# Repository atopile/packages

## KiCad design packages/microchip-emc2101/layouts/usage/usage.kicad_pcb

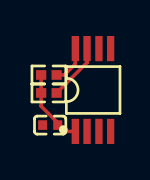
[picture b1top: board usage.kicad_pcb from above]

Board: 2 copper layers, 4 parts (0 on the bottom side), 4 nets.

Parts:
C1: [capacitance: unknown]; C0402
R1, R2: [resistance: unknown]; R0402
U1: MSOP-8_L3.0-W3.0-P0.65-LS4.9-BL

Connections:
SCL: R1.1, U1.8
SDA: R2.1, U1.7
hv: C1.1, R1.2, R2.2, U1.1
lv: C1.2, U1.5

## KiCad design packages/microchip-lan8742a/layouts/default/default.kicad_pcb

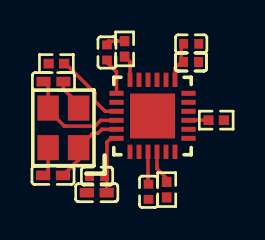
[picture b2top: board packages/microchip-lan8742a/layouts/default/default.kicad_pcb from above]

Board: 2 copper layers, 15 parts (0 on the bottom side), 9 nets.

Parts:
C1, C2, C3, C4: 1F; C0402
C5, C6: 1e-06F; C0402
C7: 4.7e-F; C0402
C8, C9: 1.8e-F; C0402
R1, R3: 100000Ω; R0402
R2: 12100Ω; R0402
R4: 10000Ω; R0402
U1: QFN-24_L4.0-W4.0-P0.50-TL-EP2.5
X1: OSC-SMD_4P-L3.2-W2.5-BL_SIT8008BI

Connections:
10: R1.1, U1.10
ETH_LED_LINK: R3.1, U1.3
RBIAS: R2.1, U1.24
decoupling_3v3_bulk-power-hv: C1.1, C2.1, C3.1, C4.1, C5.1, R4.2, U1.1, U1.9, U1.19
hv: C6.1, C7.1, U1.6
lv: C1.2, C2.2, C3.2, C4.2, C5.2, C6.2, C7.2, C8.2, C9.2, R1.2, R2.2, R3.2, U1.25, X1.2, X1.4
nRST: R4.1, U1.15
xtal_caps[0]-power-hv: C8.1, U1.5, X1.1
xtal_caps[1]-power-hv: C9.1, U1.4, X1.3

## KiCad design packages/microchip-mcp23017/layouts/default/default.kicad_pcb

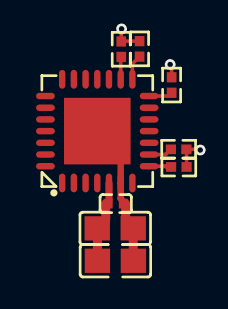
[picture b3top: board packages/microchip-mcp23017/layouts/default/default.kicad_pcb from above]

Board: 2 copper layers, 9 parts (0 on the bottom side), 7 nets.

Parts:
C1: 1F; C0402
C2, C3: 9.999F; C0805
R1, R2, R3, R4, R5: 10000Ω; R0402
U1: QFN-28_L6.0-W6.0-P0.65-BL-EP3.7

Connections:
INTA: R2.1, U1.16
INTB: R3.1, U1.15
SCL: R4.1, U1.8
SDA: R5.1, U1.9
hv: C1.1, C2.1, C3.1, R1.2, R2.2, R3.2, R4.2, R5.2, U1.5
lv: C1.2, C2.2, C3.2, U1.6, U1.11, U1.12, U1.13, U1.29
nRESET: R1.1, U1.14

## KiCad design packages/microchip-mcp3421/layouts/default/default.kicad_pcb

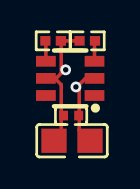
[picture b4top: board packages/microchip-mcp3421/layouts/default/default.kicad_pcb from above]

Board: 2 copper layers, 5 parts (0 on the bottom side), 4 nets.

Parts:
C1: 1F; C0402
C2: 9.999F; C0805
R1, R2: 4700Ω; R0402
U1: SOT-23-6_L2.9-W1.6-P0.95-LS2.8-BR

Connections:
SCL: R1.1, U1.3
SDA: R2.1, U1.4
hv: C1.1, C2.1, R1.2, R2.2, U1.5
lv: C1.2, C2.2, U1.2
